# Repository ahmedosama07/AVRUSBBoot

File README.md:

# AVRUSBBoot
USB bootloader for Atmel AVR controllers

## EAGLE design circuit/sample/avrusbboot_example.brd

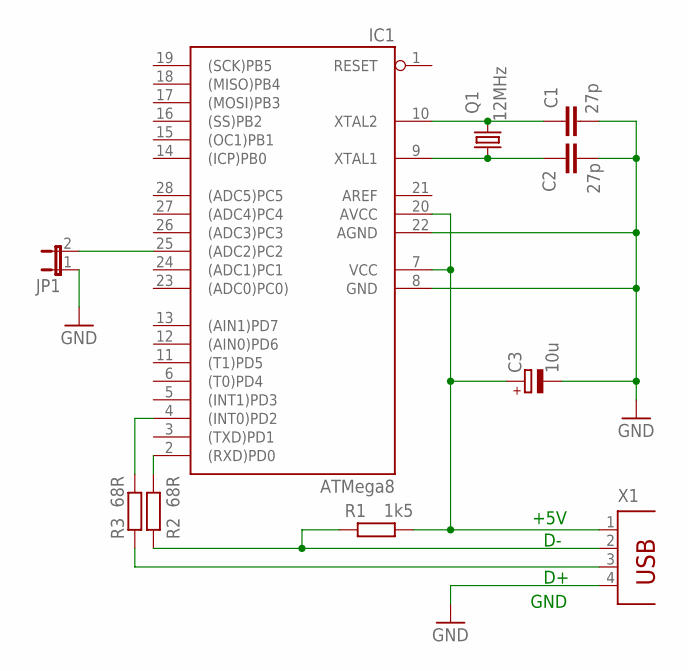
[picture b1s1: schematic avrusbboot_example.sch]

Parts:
C1, C2: 27p; C025-024X044
C3: 10u; E2,5-5
IC1: ATMega8; DIL28-3
JP1: JP1E; JP1
Q1: 12MHz; HC49/S
R1: 1k5; 0207/7
R2, R3: 68R; 0207/7
X1: PN61729

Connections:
AREF: IC1.21 (AREF)
D_N: R1.1, R2.1, X1.2
D_P: R3.1, X1.3
GND: C1.2, C2.2, C3.-, IC1.8 (GND), IC1.22 (AGND), JP1.1, X1.4
unnamed: IC1.25 ((ADC2)PC2), JP1.2
unnamed: C1.1, IC1.10 (XTAL2), Q1.2
unnamed: C2.1, IC1.9 (XTAL1), Q1.1
R_N: IC1.2 ((RXD)PD0), R2.2
R_P: IC1.4 ((INT0)PD2), R3.2
VCC: C3.+, IC1.7 (VCC), IC1.20 (AVCC), R1.2, X1.1

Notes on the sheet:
+5V
GND

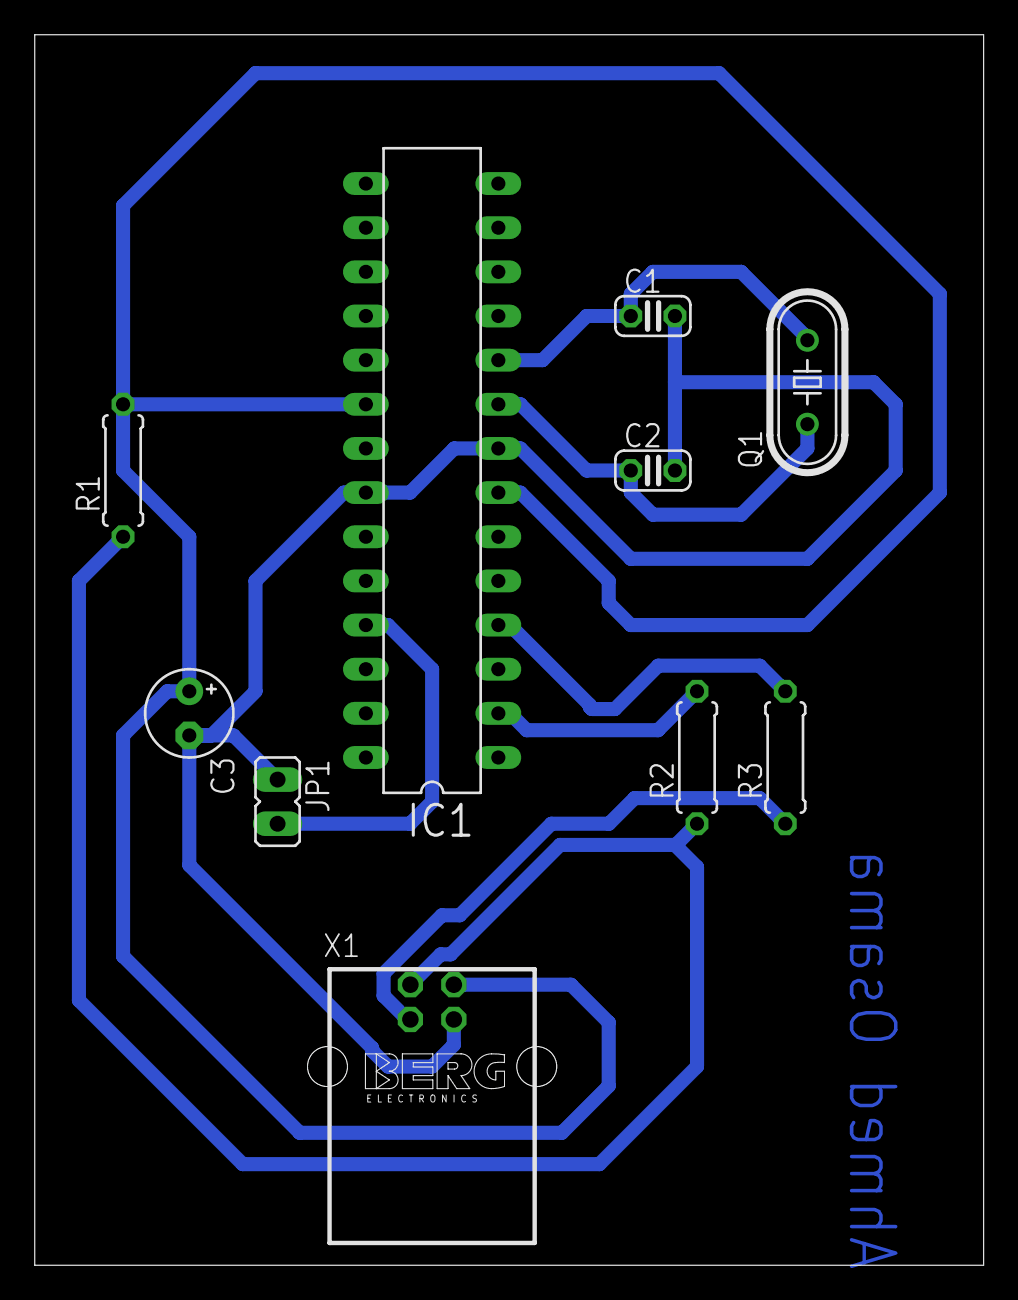
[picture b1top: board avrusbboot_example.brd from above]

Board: 2 copper layers, 54.6 x 70.8 mm, 10 parts (0 on the bottom side), 9 nets.

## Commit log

2023-11-07 compiled
2023-11-27 Simple PCB
2023-11-27 sample board
2023-12-02 schematic
2023-12-02 Connectors
2023-12-03 usbasp programmer
2023-12-03 clean
2023-12-03 build
2023-12-03 routing pcb
2023-12-03 software tests
2023-12-03 pcb trial
2023-12-03 Revert "pcb trial"
    This reverts commit de32394c14970a8398b5581bec110614df603549.
2023-12-03 Revert "schematic without routing"
2023-12-04 Update issue templates
2023-12-10 fix windows error
    in Visual Studio when running this method caused an error pointed by @ziadelbouriny
2023-12-29 Windows tool
2023-12-29 update logging
2023-12-29 kicad schematics
2023-12-30 cleaning
2023-12-30 release
